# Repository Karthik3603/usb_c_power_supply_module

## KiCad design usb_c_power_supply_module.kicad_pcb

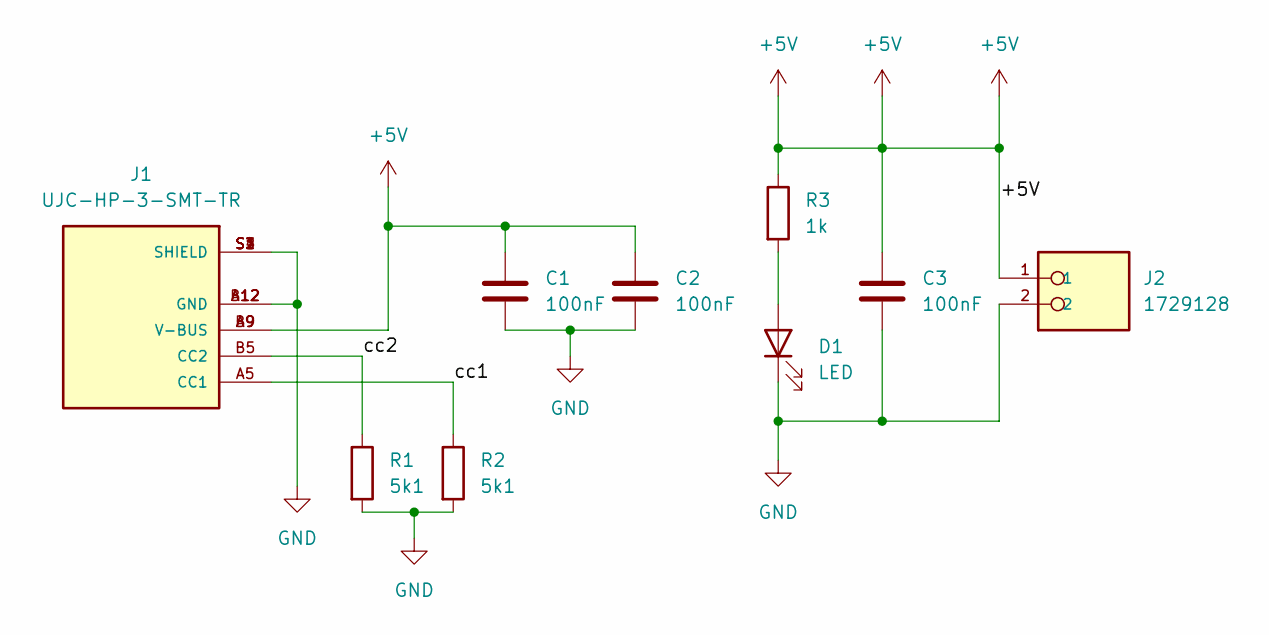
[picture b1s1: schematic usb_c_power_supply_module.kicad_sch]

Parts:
C1, C2, C3: 100nF; C_0603_1608Metric
D1: LED; LED_1206_3216Metric
J1: UJC-HP-3-SMT-TR; CUI_UJC-HP-3-SMT-TR; PARTREV 04/30/2020
J2: 1729128; PHOENIX_1729128; PARTREV 28.07.2023
R1, R2: 5k1; R_0805_2012Metric
R3: 1k; R_0805_2012Metric

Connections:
+5V: C1.1, C2.1, C3.1, J1.A9 (V-BUS), J1.B9 (V-BUS), J2.1, R3.1
/cc1: J1.A5 (CC1), R2.1
/cc2: J1.B5 (CC2), R1.1
GND: C1.2, C2.2, C3.2, D1.1 (K), J1.A12 (GND), J1.B12 (GND), J1.S1 (SHIELD), J1.S2 (SHIELD), J1.S3 (SHIELD), J1.S4 (SHIELD), J2.2, R1.2, R2.2
unnamed: D1.2 (A), R3.2

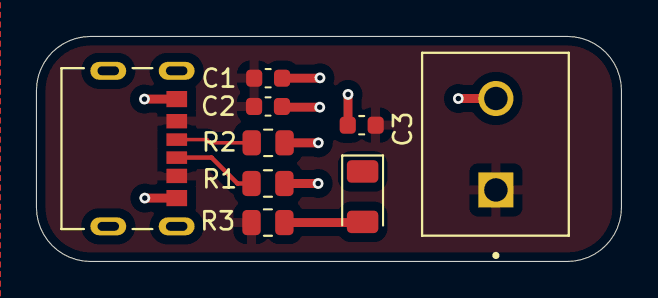
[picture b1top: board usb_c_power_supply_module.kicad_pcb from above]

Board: 2 copper layers, 32.5 x 12.5 mm, 9 parts (0 on the bottom side), 5 nets.

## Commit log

2025-03-02 Power_delivery_module
